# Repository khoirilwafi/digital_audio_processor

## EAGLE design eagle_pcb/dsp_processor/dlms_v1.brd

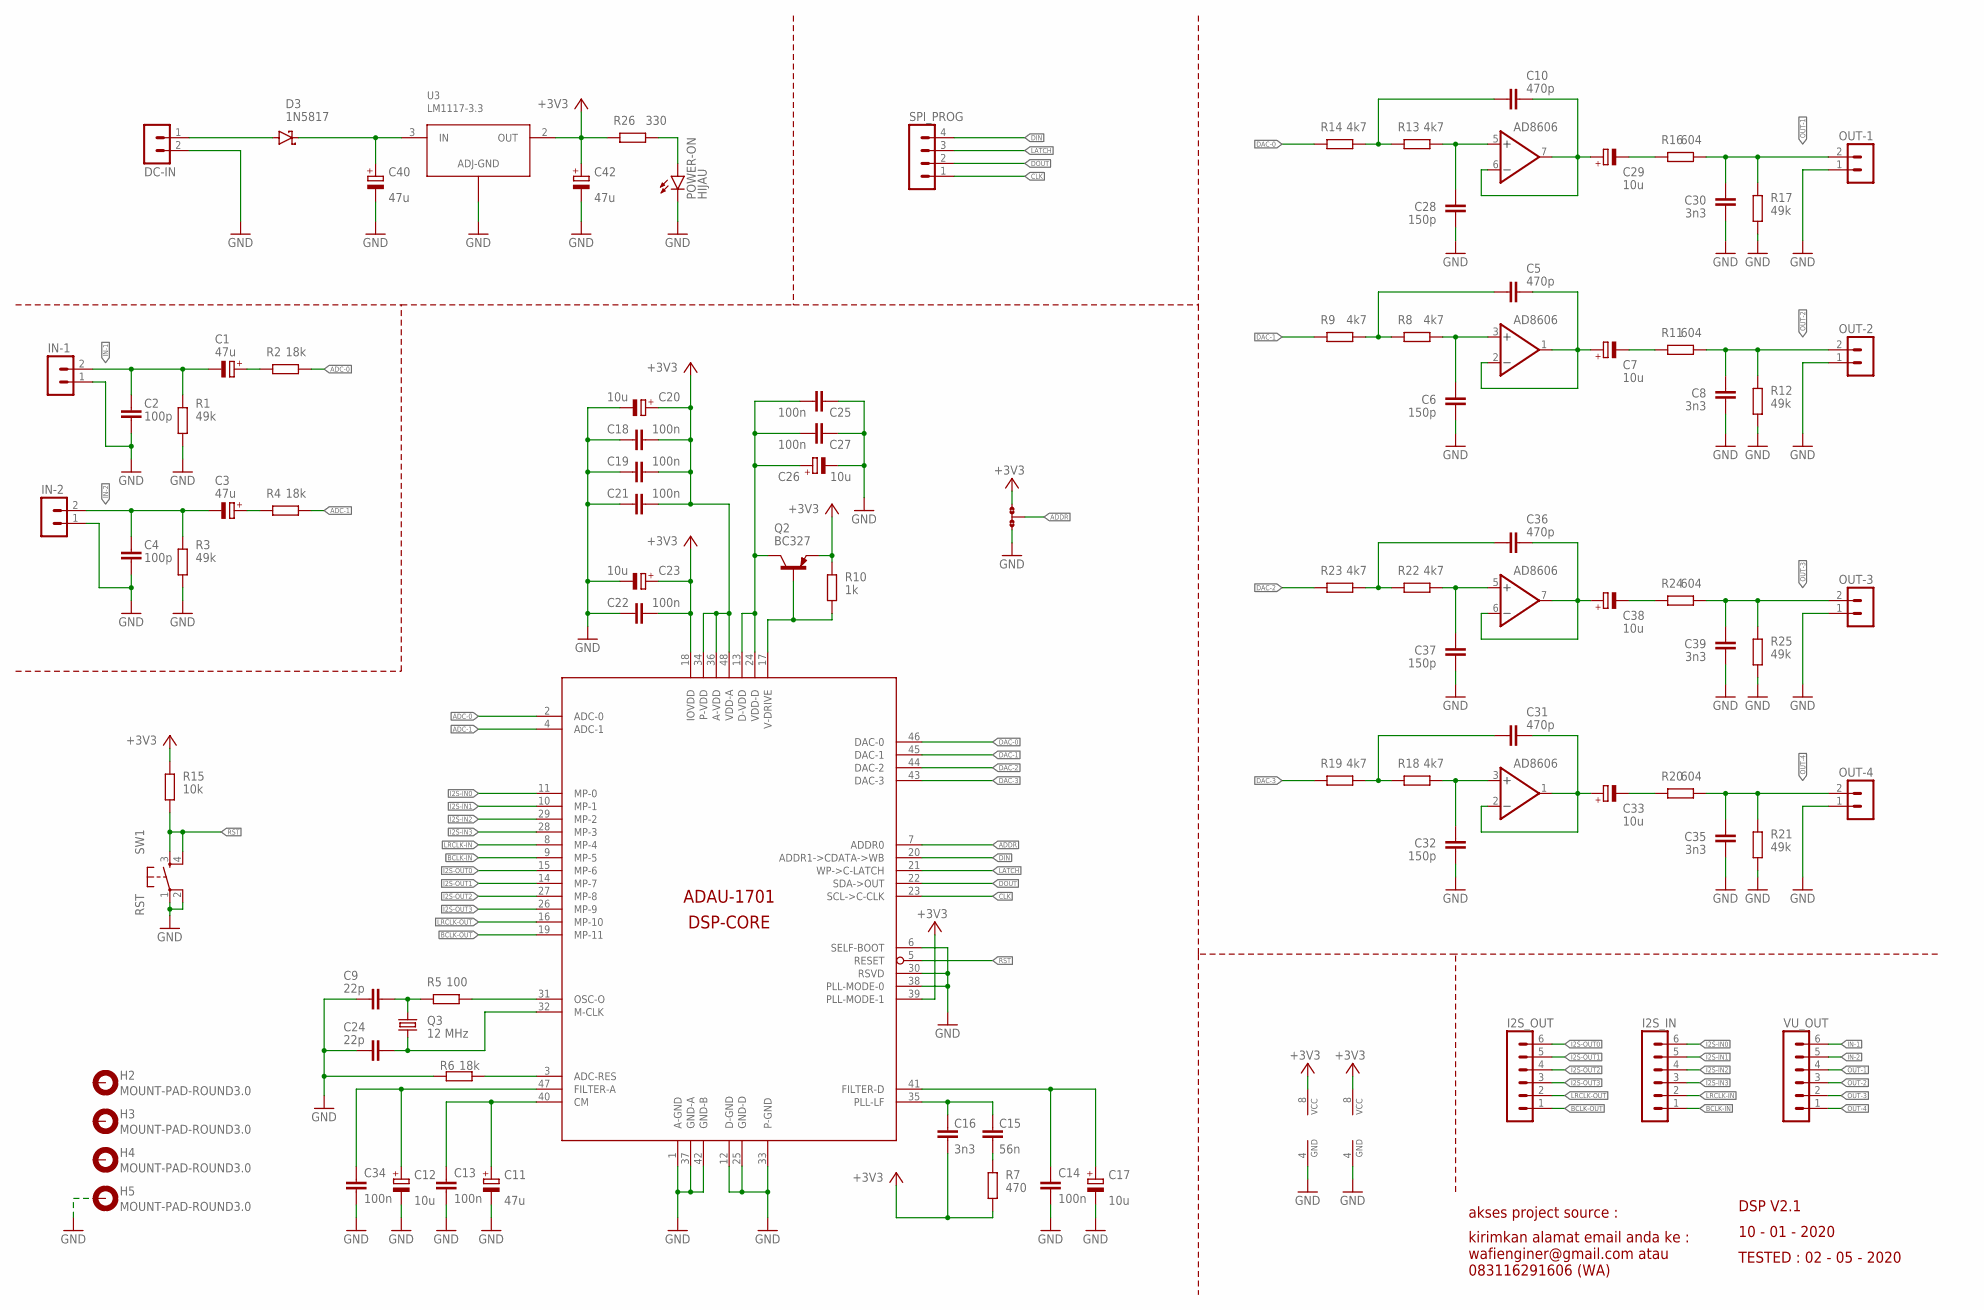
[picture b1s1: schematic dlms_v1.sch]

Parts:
ADDR: 0R-JUMPA; A0R-JMP
C1, C3, C11, C40, C42: 47u; E2,5-5
C2, C4: 100p; C050-024X044
C5, C10, C31, C36: 470p; C050-024X044
C6, C28, C32, C37: 150p; C050-024X044
C7, C12, C17, C20, C23, C26, C29, C33, C38: 10u; E2,5-5
C8, C16, C30, C35, C39: 3n3; C050-024X044
C9, C24: 22p; 0805
C13, C14, C18, C19, C21, C22, C25, C27, C34: 100n; 0805
C15: 56n; C050-024X044
D3: 1N5817; DO35Z7
DC-IN: MOLEX-2; 6410-02
H2, H3, H4, H5: MOUNT-PAD-ROUND3.0; 3,0-PAD
I2S_IN, I2S_OUT: MOLEX-6; 6410-06
IC1, IC2: AD8606; SOP8
IN-1, IN-2: MOLEX-2; 6410-02
OUT-1, OUT-2, OUT-3, OUT-4: MOLEX-2; 6410-02
POWER-ON: HIJAU; LED3MM
Q2: BC327; TO92-EBC
Q3: 12 MHz; HC49UP
R1, R3, R12, R17, R21, R25: 49k; 0204/7
R2, R4, R6: 18k; 0204/7
R5: 100; 0204/7
R7: 470; 0204/7
R8, R9, R13, R14, R18, R19, R22, R23: 4k7; 0204/7
R10: 1k; 0204/7
R11, R16, R20, R24: 604; 0204/7
R15: 10k; 0204/7
R26: 330; 0204/7
RST: SW1; B3F-10XX
SPI_PROG: MOLEX-4; 6410-04
U1: ADAU-1701; LQFP-48
U3: LM1117-3.3; TO220H
VU_OUT: MOLEX-6; 6410-06

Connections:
+3V3: ADDR.1, C16.2, C18.P$1 (1), C19.P$1 (1), C20.+, C21.P$1 (1), C22.P$1 (1), C23.+, C42.+, IC1.8 (VCC), IC2.8 (VCC), Q2.E, R7.1, R10.2, R15.2, R26.1, U1.18 (IOVDD), U1.34 (P-VDD), U1.36 (A-VDD), U1.39 (PLL-MODE-1), U1.48 (VDD-A), U3.2 (OUT)
ADC-0: R2.2, U1.2 (ADC-0)
ADC-1: R4.2, U1.4 (ADC-1)
ADDR: ADDR.2, U1.7 (ADDR0)
BCLK-IN: I2S_IN.1, U1.9 (MP-5)
BCLK-OUT: I2S_OUT.1, U1.19 (MP-11)
CLK: SPI_PROG.1, U1.23 (SCL->C-CLK)
CM: C11.+, C13.P$1 (1), U1.40 (CM)
DAC-0: R14.1, U1.46 (DAC-0)
DAC-1: R9.1, U1.45 (DAC-1)
DAC-2: R23.1, U1.44 (DAC-2)
DAC-3: R19.1, U1.43 (DAC-3)
DIN: SPI_PROG.4, U1.20 (ADDR1->CDATA->WB)
DOUT: SPI_PROG.2, U1.22 (SDA->OUT)
DVDD: C25.P$1 (1), C26.+, C27.P$1 (1), Q2.C, U1.13 (D-VDD), U1.24 (VDD-D)
FIL-A: C12.+, C34.P$1 (1), U1.47 (FILTER-A)
FIL-D: C14.P$1 (1), C17.+, U1.41 (FILTER-D)
GND: ADDR.3, C2.2, C4.2, C6.1, C8.2, C9.P$2 (2), C11.-, C12.-, C13.P$2 (2), C14.P$2 (2), C17.-, C18.P$2 (2), C19.P$2 (2), C20.-, C21.P$2 (2), C22.P$2 (2), C23.-, C24.P$2 (2), C25.P$2 (2), C26.-, C27.P$2 (2), C28.1, C30.2, C32.1, C34.P$2 (2), C35.2, C37.1, C39.2, C40.-, C42.-, DC-IN.2, H5.B3,0, IC1.4 (GND), IC2.4 (GND), IN-1.1, IN-2.1, OUT-1.1, OUT-2.1, OUT-3.1, OUT-4.1, POWER-ON.K (C), R1.1, R3.1, R6.1, R12.1, R17.1, R21.1, R25.1, RST.1, RST.2 (P1), U1.1 (A-GND), U1.6 (SELF-BOOT), U1.12 (D-GND), U1.25 (GND-D), U1.30 (RSVD), U1.33 (P-GND), U1.37 (GND-A), U1.38 (PLL-MODE-0), U1.42 (GND-B), U3.1 (GND)
I2S-IN0: I2S_IN.6, U1.11 (MP-0)
I2S-IN1: I2S_IN.5, U1.10 (MP-1)
I2S-IN2: I2S_IN.4, U1.29 (MP-2)
I2S-IN3: I2S_IN.3, U1.28 (MP-3)
I2S-OUT0: I2S_OUT.6, U1.15 (MP-6)
I2S-OUT1: I2S_OUT.5, U1.14 (MP-7)
I2S-OUT2: I2S_OUT.4, U1.27 (MP-8)
I2S-OUT3: I2S_OUT.3, U1.26 (MP-9)
IN-1: C1.-, C2.1, IN-1.2, R1.2, VU_OUT.6
IN-2: C3.-, C4.1, IN-2.2, R3.2, VU_OUT.5
LATCH: SPI_PROG.3, U1.21 (WP->C-LATCH)
LRCLK-IN: I2S_IN.2, U1.8 (MP-4)
LRCLK-OUT: I2S_OUT.2, U1.16 (MP-10)
unnamed: C1.+, R2.1
unnamed: C3.+, R4.1
unnamed: C5.1, R8.1, R9.2
unnamed: C6.2, IC1.3 (+IN), R8.2
unnamed: C5.2, C7.+, IC1.1 (OUT), IC1.2 (-IN)
unnamed: C7.-, R11.1
unnamed: C10.1, R13.1, R14.2
unnamed: C9.P$1 (1), Q3.2, R5.1
unnamed: C24.P$1 (1), Q3.1, U1.32 (M-CLK)
unnamed: R5.2, U1.31 (OSC-O)
unnamed: C28.2, IC1.5 (+IN), R13.2
unnamed: C10.2, C29.+, IC1.6 (-IN), IC1.7 (OUT)
unnamed: R6.2, U1.3 (ADC-RES)
unnamed: C29.-, R16.1
unnamed: C15.2, R7.2
unnamed: C31.1, R18.1, R19.2
unnamed: C32.2, IC2.3 (+IN), R18.2
unnamed: C31.2, C33.+, IC2.1 (OUT), IC2.2 (-IN)
unnamed: C33.-, R20.1
unnamed: C36.1, R22.1, R23.2
unnamed: C37.2, IC2.5 (+IN), R22.2
unnamed: C36.2, C38.+, IC2.6 (-IN), IC2.7 (OUT)
unnamed: C38.-, R24.1
unnamed: C40.+, D3.C, U3.3 (IN)
unnamed: POWER-ON.A, R26.2
OUT-1: C30.1, OUT-1.2, R16.2, R17.2, VU_OUT.4
OUT-2: C8.1, OUT-2.2, R11.2, R12.2, VU_OUT.3
OUT-3: C39.1, OUT-3.2, R24.2, R25.2, VU_OUT.2
OUT-4: C35.1, OUT-4.2, R20.2, R21.2, VU_OUT.1
PLL-LF: C15.1, C16.1, U1.35 (PLL-LF)
RST: R15.1, RST.3 (S), RST.4 (S1), U1.5 (RESET)
VDRIVE: Q2.B, R10.1, U1.17 (V-DRIVE)
VIN: D3.A, DC-IN.1

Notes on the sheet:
akses project source :
kirimkan alamat email anda ke : wafienginer@gmail.com atau 083116291606 (WA)
DSP V2.1
10 - 01 - 2020
TESTED : 02 - 05 - 2020

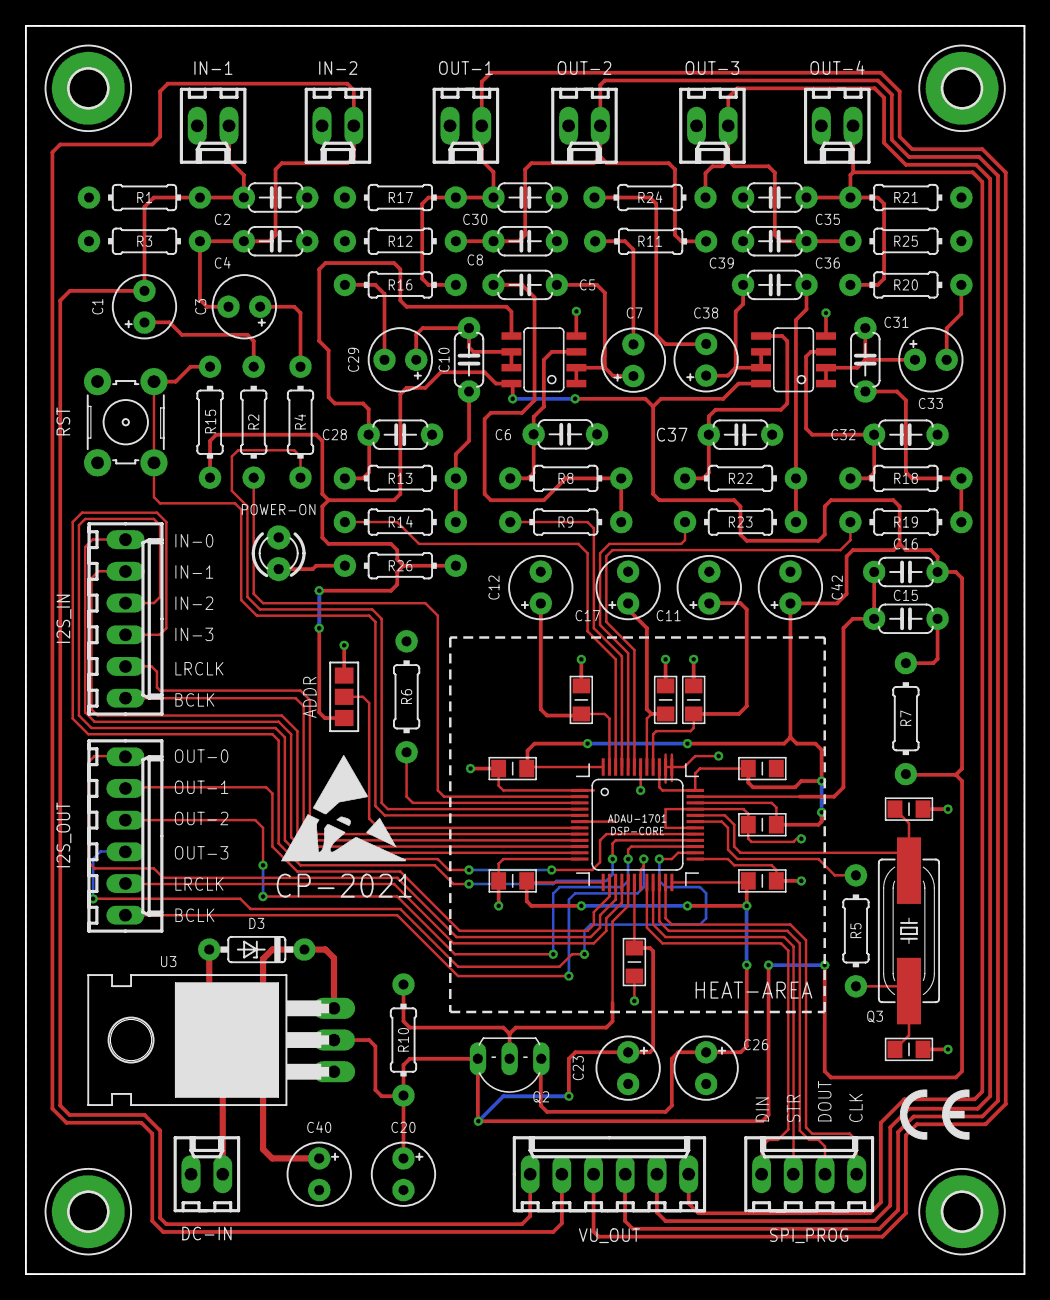
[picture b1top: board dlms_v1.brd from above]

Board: 2 copper layers, 80.0 x 100.0 mm, 94 parts (0 on the bottom side), 64 nets.

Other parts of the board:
U$2: CE-4MM
U$3: ESD_10.00

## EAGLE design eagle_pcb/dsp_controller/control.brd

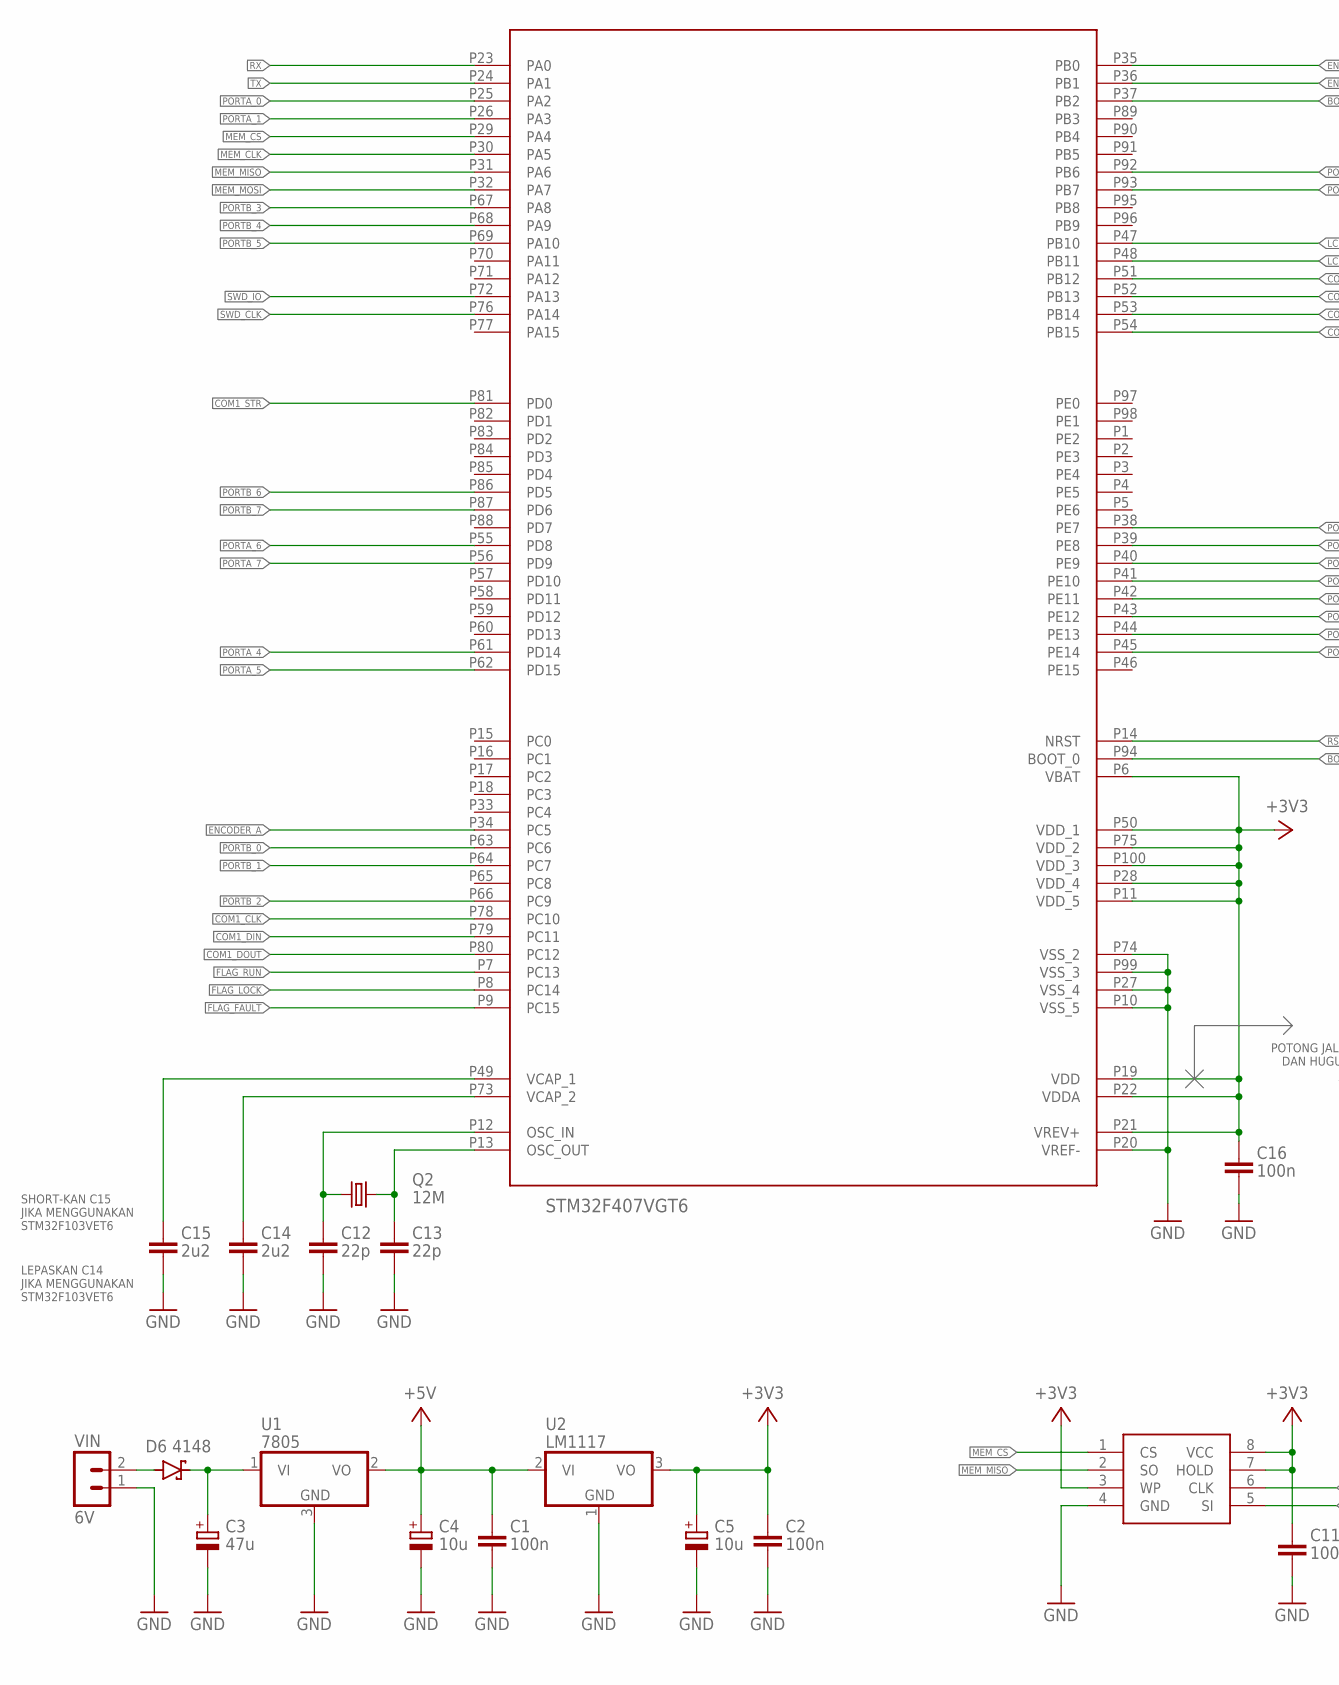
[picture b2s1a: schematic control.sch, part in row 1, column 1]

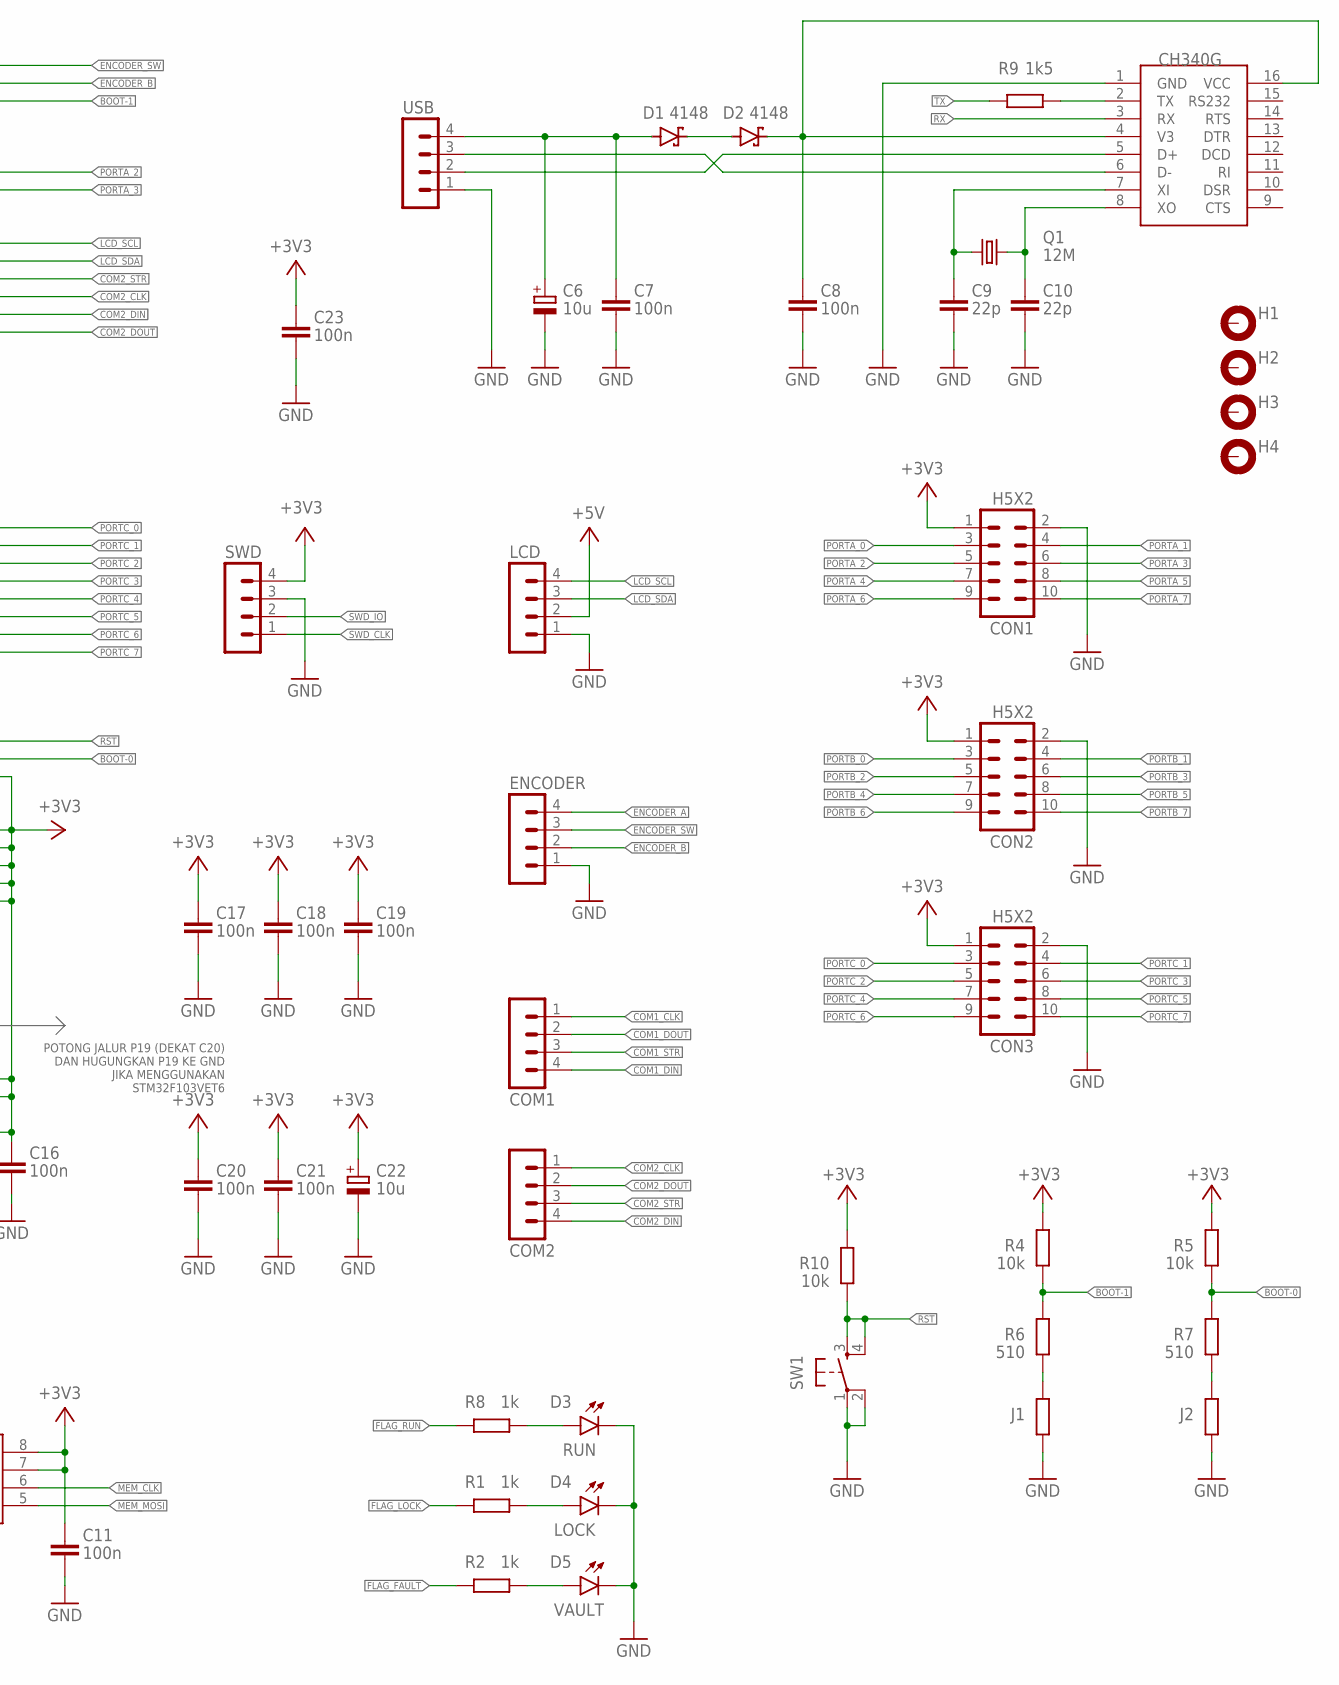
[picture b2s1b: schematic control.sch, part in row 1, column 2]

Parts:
C1, C2, C7, C8, C11, C16, C17, C18, C19, C20, C21, C23: 100n; 0805
C3: 47u; E2,5-5
C4, C5, C6, C22: 10u; E2,5-5
C9, C10, C12, C13: 22p; 0805
C14, C15: 2u2; 0805
COM1, COM2: MOLEX-4; 6410-04
CON1, CON2, CON3: H5X2; MA05-2
D1, D2, D6: 4148; DO35Z7
D3: RUN; LED3MM
D4: LOCK; LED3MM
D5: VAULT; LED3MM
ENCODER: MOLEX-4; 6410-04
H1, H2, H3, H4: MOUNT-PAD-ROUND3.0; 3,0-PAD
J1, J2: 10k; 0805
LCD: MOLEX-4; 6410-04
Q1, Q2: 12M; HC49/S
R1, R2, R8: 1k; 0805
R4, R5, R10: 10k; 0805
R6, R7: 510; 0805
R9: 1k5; 0204/7
SW1: SW; B3F-10XX
SWD: MOLEX-4; 6410-04
U1: 7805; TO252
U2: LM1117; TO252
U3: W25QXX; SOP8
U4: STM32F407; LQFP100
U$1: CH340G; SOIC16
USB: MOLEX-4; 6410-04
VIN: 6V; 6410-02

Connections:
+3V3: C2.P$1 (1), C5.+, C11.P$1 (1), C16.P$1 (1), C17.P$1 (1), C18.P$1 (1), C19.P$1 (1), C20.P$1 (1), C21.P$1 (1), C22.+, C23.P$1 (1), CON1.1, CON2.1, CON3.1, R4.P$2 (2), R5.P$2 (2), R10.P$2 (2), SWD.4, U2.3 (VO), U3.3 (WP), U3.7 (HOLD), U3.8 (VCC), U4.P6 (VBAT), U4.P11 (VDD_5), U4.P19 (VDD), U4.P21 (VREV+), U4.P22 (VDDA), U4.P28 (VDD_4), U4.P50 (VDD_1), U4.P75 (VDD_2), U4.P100 (VDD_3)
+5V: C1.P$1 (1), C4.+, LCD.2, U1.2 (VO), U2.2 (VI)
BOOT-0: R5.P$1 (1), R7.P$2 (2), U4.P94 (BOOT_0)
BOOT-1: R4.P$1 (1), R6.P$2 (2), U4.P37 (PB2)
COM1_CLK: COM1.1, U4.P78 (PC10)
COM1_DIN: COM1.4, U4.P79 (PC11)
COM1_DOUT: COM1.2, U4.P80 (PC12)
COM1_STR: COM1.3, U4.P81 (PD0)
COM2_CLK: COM2.1, U4.P52 (PB13)
COM2_DIN: COM2.4, U4.P53 (PB14)
COM2_DOUT: COM2.2, U4.P54 (PB15)
COM2_STR: COM2.3, U4.P51 (PB12)
ENCODER_A: ENCODER.4, U4.P34 (PC5)
ENCODER_B: ENCODER.2, U4.P36 (PB1)
ENCODER_SW: ENCODER.3, U4.P35 (PB0)
FLAG_FAULT: R2.P$2 (2), U4.P9 (PC15)
FLAG_LOCK: R1.P$2 (2), U4.P8 (PC14)
FLAG_RUN: R8.P$2 (2), U4.P7 (PC13)
GND: C1.P$2 (2), C2.P$2 (2), C3.-, C4.-, C5.-, C6.-, C7.P$2 (2), C8.P$2 (2), C9.P$2 (2), C10.P$2 (2), C11.P$2 (2), C12.P$2 (2), C13.P$2 (2), C14.P$2 (2), C15.P$2 (2), C16.P$2 (2), C17.P$2 (2), C18.P$2 (2), C19.P$2 (2), C20.P$2 (2), C21.P$2 (2), C22.-, C23.P$2 (2), CON1.2, CON2.2, CON3.2, D3.K (C), D4.K (C), D5.K (C), ENCODER.1, J1.P$1 (1), J2.P$1 (1), LCD.1, SW1.1, SW1.2 (P1), SWD.3, U1.3 (GND), U2.1 (GND), U3.4 (GND), U4.P10 (VSS_5), U4.P20 (VREF-), U4.P27 (VSS_4), U4.P74 (VSS_2), U4.P99 (VSS_3), U$1.1 (GND), USB.1, VIN.1
LCD_SCL: LCD.4, U4.P47 (PB10)
LCD_SDA: LCD.3, U4.P48 (PB11)
MEM_CLK: U3.6 (CLK), U4.P30 (PA5)
MEM_CS: U3.1 (CS), U4.P29 (PA4)
MEM_MISO: U3.2 (SO), U4.P31 (PA6)
MEM_MOSI: U3.5 (SI), U4.P32 (PA7)
unnamed: C3.+, D6.C, U1.1 (VI)
unnamed: C6.+, C7.P$1 (1), D1.A, USB.4
unnamed: D1.C, D2.A
unnamed: C8.P$1 (1), D2.C, U$1.4 (V3), U$1.16 (VCC)
unnamed: U$1.6 (D-), USB.3
unnamed: U$1.5 (D+), USB.2
unnamed: C9.P$1 (1), Q1.1, U$1.7 (XI)
unnamed: C10.P$1 (1), Q1.2, U$1.8 (XO)
unnamed: D5.A, R2.P$1 (1)
unnamed: D4.A, R1.P$1 (1)
unnamed: D3.A, R8.P$1 (1)
unnamed: C12.P$1 (1), Q2.1, U4.P12 (OSC_IN)
unnamed: C13.P$1 (1), Q2.2, U4.P13 (OSC_OUT)
unnamed: C14.P$1 (1), U4.P73 (VCAP_2)
unnamed: C15.P$1 (1), U4.P49 (VCAP_1)
unnamed: D6.A, VIN.2
unnamed: J1.P$2 (2), R6.P$1 (1)
unnamed: J2.P$2 (2), R7.P$1 (1)
unnamed: R9.2, U$1.2 (TX)
PORTA_0: CON1.3, U4.P25 (PA2)
PORTA_1: CON1.4, U4.P26 (PA3)
PORTA_2: CON1.5, U4.P92 (PB6)
PORTA_3: CON1.6, U4.P93 (PB7)
PORTA_4: CON1.7, U4.P61 (PD14)
PORTA_5: CON1.8, U4.P62 (PD15)
PORTA_6: CON1.9, U4.P55 (PD8)
PORTA_7: CON1.10, U4.P56 (PD9)
PORTB_0: CON2.3, U4.P63 (PC6)
PORTB_1: CON2.4, U4.P64 (PC7)
PORTB_2: CON2.5, U4.P66 (PC9)
PORTB_3: CON2.6, U4.P67 (PA8)
PORTB_4: CON2.7, U4.P68 (PA9)
PORTB_5: CON2.8, U4.P69 (PA10)
PORTB_6: CON2.9, U4.P86 (PD5)
PORTB_7: CON2.10, U4.P87 (PD6)
PORTC_0: CON3.3, U4.P38 (PE7)
PORTC_1: CON3.4, U4.P39 (PE8)
PORTC_2: CON3.5, U4.P40 (PE9)
PORTC_3: CON3.6, U4.P41 (PE10)
PORTC_4: CON3.7, U4.P42 (PE11)
PORTC_5: CON3.8, U4.P43 (PE12)
PORTC_6: CON3.9, U4.P44 (PE13)
PORTC_7: CON3.10, U4.P45 (PE14)
RST: R10.P$1 (1), SW1.3 (S), SW1.4 (S1), U4.P14 (NRST)
RX: U4.P23 (PA0), U$1.3 (RX)
SWD_CLK: SWD.1, U4.P76 (PA14)
SWD_IO: SWD.2, U4.P72 (PA13)
TX: R9.1, U4.P24 (PA1)

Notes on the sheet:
STM32F407VGT6
SHORT-KAN C15 JIKA MENGGUNAKAN STM32F103VET6
LEPASKAN C14 JIKA MENGGUNAKAN STM32F103VET6
POTONG JALUR P19 (DEKAT C20) DAN HUGUNGKAN P19 KE GND JIKA MENGGUNAKAN STM32F103VET6

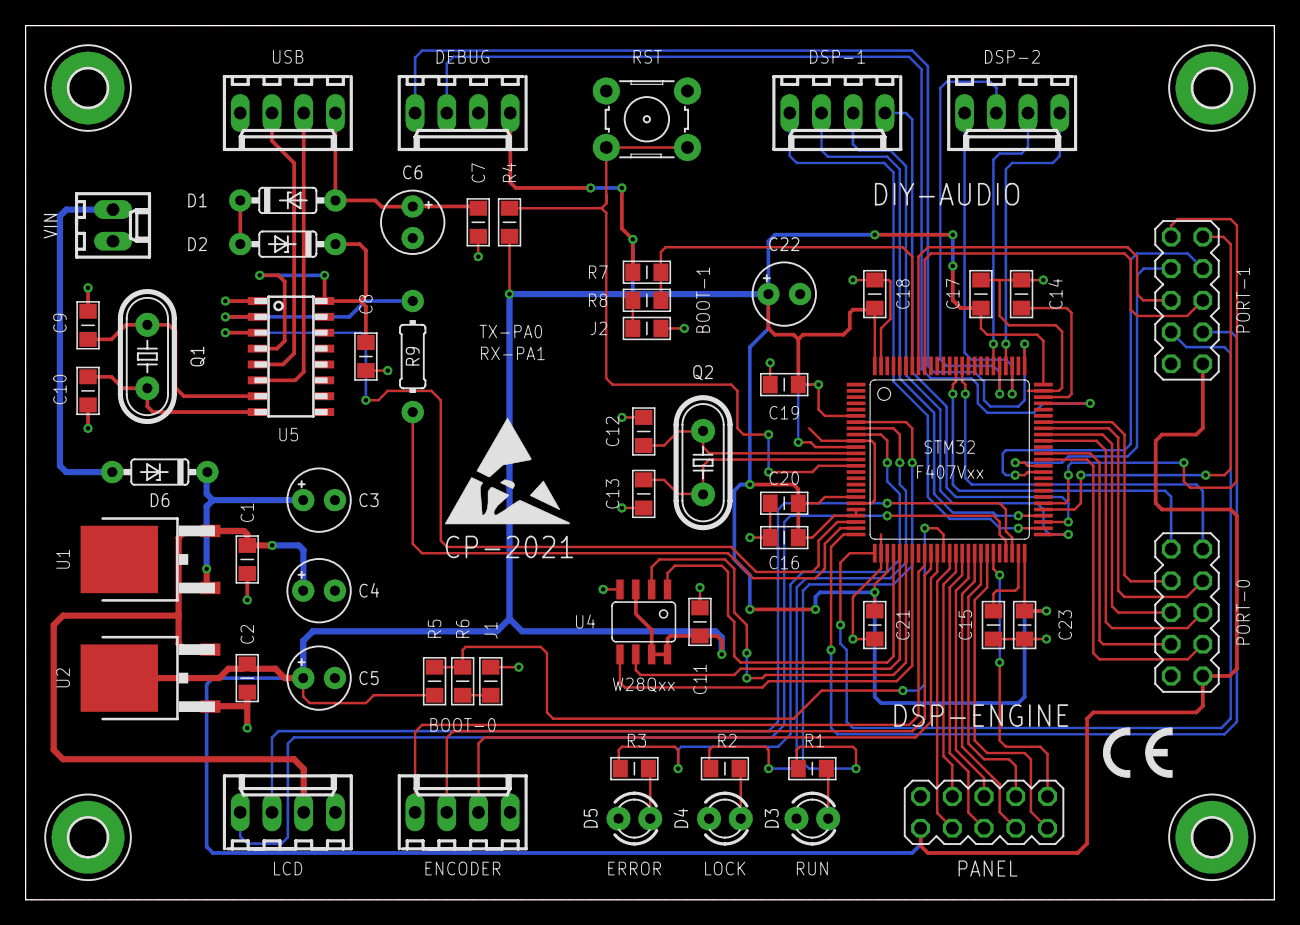
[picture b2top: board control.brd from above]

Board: 2 copper layers, 100.0 x 70.0 mm, 64 parts (0 on the bottom side), 73 nets.

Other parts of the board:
E$1: ESD_10.00
U$2: CE-4MM

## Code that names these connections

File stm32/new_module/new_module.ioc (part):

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Mcu.Name=STM32F103V(C-D-E)Tx
Mcu.Package=LQFP100
Mcu.UserName=STM32F103VETx
PA0-WKUP.GPIOParameters=GPIO_Label
PA0-WKUP.GPIO_Label=TX
PA0-WKUP.Signal=GPIO_Output
PA10.GPIOParameters=PinState,GPIO_Label
PA10.GPIO_Label=OUT3-MUTE
PA10.PinState=GPIO_PIN_SET
PA10.Signal=GPIO_Output
PA13.Mode=Serial_Wire
PA13.Signal=SYS_JTMS-SWDIO
PA14.Mode=Serial_Wire
PA14.Signal=SYS_JTCK-SWCLK
PA2.GPIOParameters=PinState,GPIO_Label
PA2.GPIO_Label=OUT1-SEL
PA2.PinState=GPIO_PIN_SET
PA2.Signal=GPIO_Output
PA3.GPIOParameters=PinState,GPIO_Label
PA3.GPIO_Label=OUT1-MUTE
PA3.PinState=GPIO_PIN_SET
PA3.Signal=GPIO_Output
PA4.GPIOParameters=GPIO_Speed,GPIO_Label
PA4.GPIO_Label=SPI1_CS
PA4.GPIO_Speed=GPIO_SPEED_FREQ_HIGH
PA4.Signal=GPIO_Output
PA5.Mode=Full_Duplex_Master
PA5.Signal=SPI1_SCK
PA6.Mode=Full_Duplex_Master
PA6.Signal=SPI1_MISO
PA7.Mode=Full_Duplex_Master
PA7.Signal=SPI1_MOSI
PA8.GPIOParameters=PinState,GPIO_Label
PA8.GPIO_Label=OUT4-MUTE
PA8.PinState=GPIO_PIN_SET
PA8.Signal=GPIO_Output
PA9.GPIOParameters=PinState,GPIO_Label
PA9.GPIO_Label=OUT3-SEL
PA9.PinState=GPIO_PIN_SET
PA9.Signal=GPIO_Output
PB0.GPIOParameters=GPIO_PuPd,GPIO_Label
PB0.GPIO_Label=ENA
PB0.GPIO_PuPd=GPIO_PULLUP
PB0.Signal=GPIO_Input
PB1.GPIOParameters=GPIO_PuPd,GPIO_Label
PB1.GPIO_Label=ENB
PB1.GPIO_PuPd=GPIO_PULLUP
PB1.Signal=GPIO_Input
PB10.GPIOParameters=GPIO_Pu
PB10.GPIO_Pu=GPIO_PULLUP
PB10.Mode=I2C
PB10.Signal=I2C2_SCL
PB11.GPIOParameters=GPIO_Pu
PB11.GPIO_Pu=GPIO_PULLUP
PB11.Mode=I2C
PB11.Signal=I2C2_SDA
PB12.GPIOParameters=GPIO_Speed,GPIO_Label
PB12.GPIO_Label=SPI2_CS
PB12.GPIO_Speed=GPIO_SPEED_FREQ_HIGH
PB12.Signal=GPIO_Output
PB13.Mode=Full_Duplex_Master
PB13.Signal=SPI2_SCK
PB14.Mode=Full_Duplex_Master
PB14.Signal=SPI2_MISO
PB15.Mode=Full_Duplex_Master
PB15.Signal=SPI2_MOSI
PB6.GPIOParameters=PinState,GPIO_Label
PB6.GPIO_Label=IN2-SEL
PB6.PinState=GPIO_PIN_SET
PB6.Signal=GPIO_Output
PB7.GPIOParameters=PinState,GPIO_Label
PB7.GPIO_Label=IN2-MUTE
PB7.PinState=GPIO_PIN_SET
PB7.Signal=GPIO_Output
PC13-TAMPER-RTC.GPIOParameters=GPIO_Label
PC13-TAMPER-RTC.GPIO_Label=RUN
PC13-TAMPER-RTC.Signal=GPIO_Output
PC14-OSC32_IN.GPIOParameters=GPIO_Label
PC14-OSC32_IN.GPIO_Label=LOCK
PC14-OSC32_IN.Signal=GPIO_Output
PC15-OSC32_OUT.GPIOParameters=GPIO_Label
PC15-OSC32_OUT.GPIO_Label=ERROR
PC15-OSC32_OUT.Signal=GPIO_Output
PC5.GPIOParameters=GPIO_PuPd,GPIO_Label
PC5.GPIO_Label=ENSW
PC5.GPIO_PuPd=GPIO_PULLUP
PC5.Signal=GPIO_Input
PC6.GPIOParameters=GPIO_PuPd,GPIO_Label
PC6.GPIO_Label=OUT3
PC6.GPIO_PuPd=GPIO_PULLUP
PC6.Signal=GPIO_Input
PC7.GPIOParameters=GPIO_PuPd,GPIO_Label
PC7.GPIO_Label=OUT4
PC7.GPIO_PuPd=GPIO_PULLUP
PC7.Signal=GPIO_Input
PC9.GPIOParameters=PinState,GPIO_Label
PC9.GPIO_Label=OUT4-SEL
PC9.PinState=GPIO_PIN_SET
PC9.Signal=GPIO_Output
PD14.GPIOParameters=PinState,GPIO_Label
PD14.GPIO_Label=IN1-SEL
PD14.PinState=GPIO_PIN_SET
PD14.Signal=GPIO_Output
PD15.GPIOParameters=PinState,GPIO_Label
PD15.GPIO_Label=IN1-MUTE
PD15.PinState=GPIO_PIN_SET
PD15.Signal=GPIO_Output
PD5.GPIOParameters=PinState,GPIO_Label
PD5.GPIO_Label=OUT2-SEL
PD5.PinState=GPIO_PIN_SET
PD5.Signal=GPIO_Output
PD6.GPIOParameters=PinState,GPIO_Label
PD6.GPIO_Label=OUT2-MUTE
PD6.PinState=GPIO_PIN_SET
PD6.Signal=GPIO_Output
PD8.GPIOParameters=PinState,GPIO_Label,GPIO_ModeDefaultOutputPP
PD8.GPIO_Label=DSP_RST
PD8.GPIO_ModeDefaultOutputPP=GPIO_MODE_OUTPUT_OD
PD8.PinState=GPIO_PIN_SET
PD8.Signal=GPIO_Output
PE10.GPIOParameters=GPIO_PuPd,GPIO_Label
PE10.GPIO_Label=RESET
PE10.GPIO_PuPd=GPIO_PULLUP
PE10.Signal=GPIO_Input
PE11.GPIOParameters=GPIO_PuPd,GPIO_Label
PE11.GPIO_Label=IN2
PE11.GPIO_PuPd=GPIO_PULLUP
PE11.Signal=GPIO_Input
PE12.GPIOParameters=GPIO_PuPd,GPIO_Label
PE12.GPIO_Label=IN1
PE12.GPIO_PuPd=GPIO_PULLUP
PE12.Signal=GPIO_Input
PE13.GPIOParameters=GPIO_PuPd,GPIO_Label
PE13.GPIO_Label=OUT1
PE13.GPIO_PuPd=GPIO_PULLUP
PE13.Signal=GPIO_Input
PE14.GPIOParameters=GPIO_PuPd,GPIO_Label
PE14.GPIO_Label=OUT2
PE14.GPIO_PuPd=GPIO_PULLUP
PE14.Signal=GPIO_Input
PE7.GPIOParameters=GPIO_PuPd,GPIO_Label
PE7.GPIO_Label=PAGE
PE7.GPIO_PuPd=GPIO_PULLUP
PE7.Signal=GPIO_Input
PE8.GPIOParameters=GPIO_PuPd,GPIO_Label
PE8.GPIO_Label=SAVE
PE8.GPIO_PuPd=GPIO_PULLUP
PE8.Signal=GPIO_Input
PE9.GPIOParameters=GPIO_PuPd,GPIO_Label
PE9.GPIO_Label=MUTE
PE9.GPIO_PuPd=GPIO_PULLUP
PE9.Signal=GPIO_Input
RCC.HSEDivPLL=RCC_HSE_PREDIV_DIV2
RCC.HSE_VALUE=16000000
RCC.SYSCLKFreq_VALUE=72000000
RCC.SYSCLKSource=RCC_SYSCLKSOURCE_PLLCLK
board=custom
